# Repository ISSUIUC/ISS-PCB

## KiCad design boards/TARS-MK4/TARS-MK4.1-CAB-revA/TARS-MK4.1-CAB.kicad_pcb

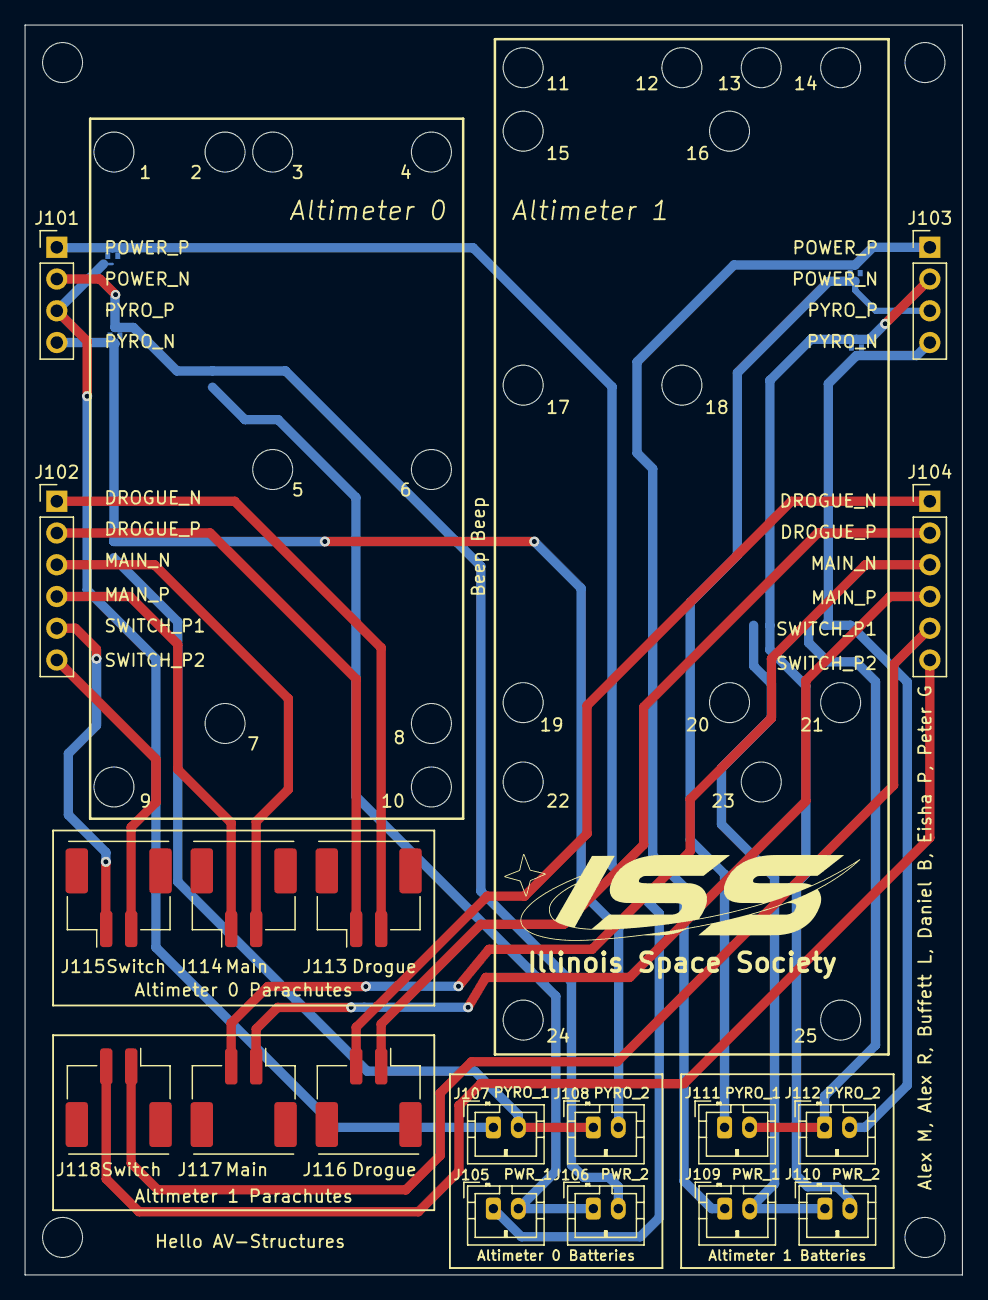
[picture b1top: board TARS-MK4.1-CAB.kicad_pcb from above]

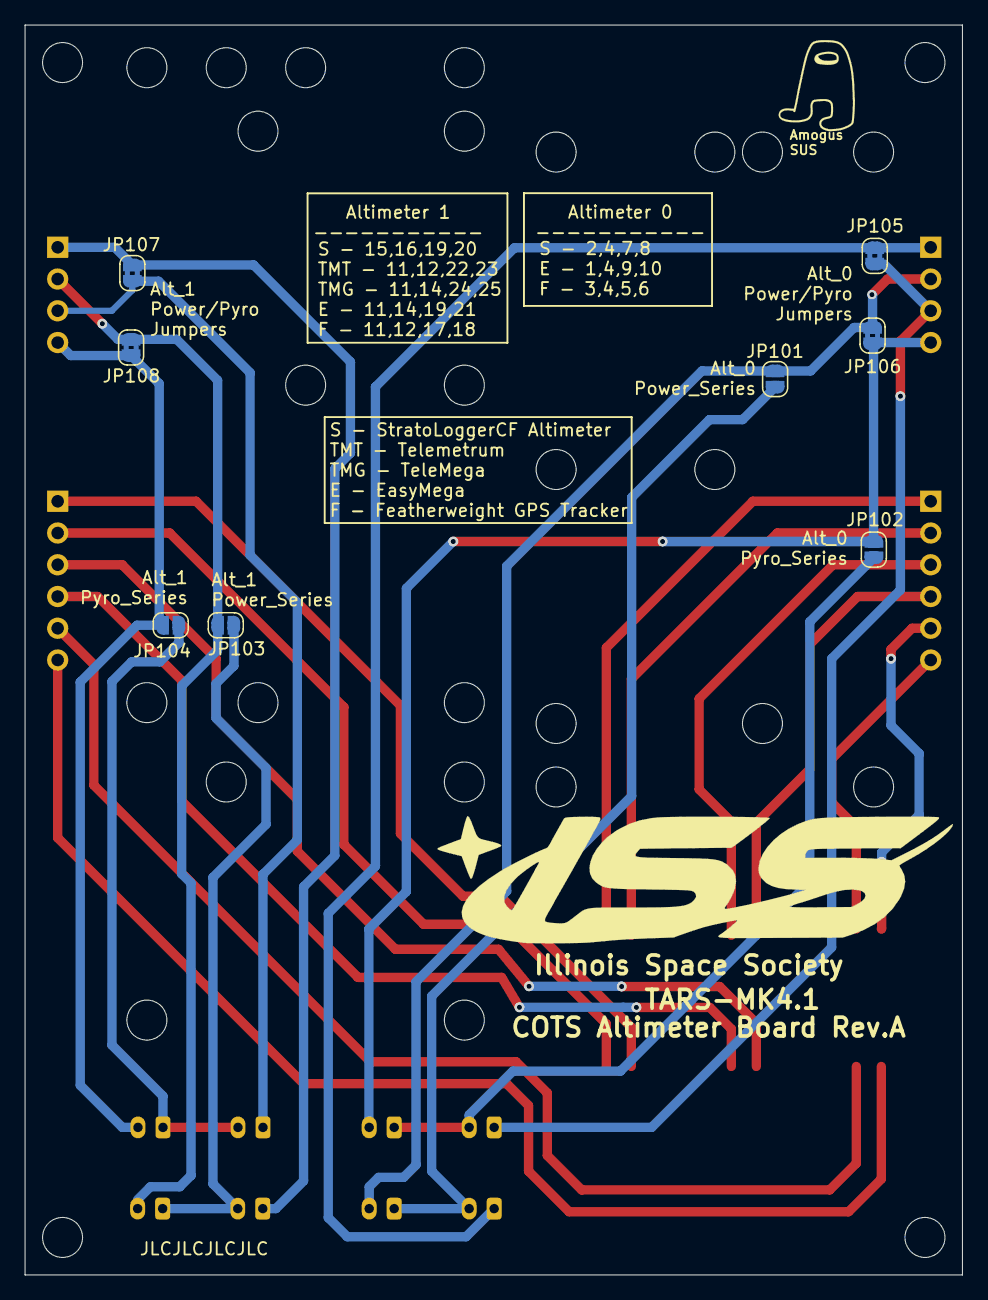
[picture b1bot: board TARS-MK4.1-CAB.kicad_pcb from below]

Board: 2 copper layers, 75.0 x 100.0 mm, 26 parts (8 on the bottom side), 24 nets.

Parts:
J101, J103: PinHeader_1x04_P2.54mm_Vertical
J102, J104: PinHeader_1x06_P2.54mm_Vertical
J105, J106, J107, J108, J109, J110, J111, J112: JST_PH_B2B-PH-K_1x02_P2.00mm_Vertical
J113, J114, J115, J116, J117, J118: Molex_CLIK-Mate_502443-0270; Molex_CLIK-Mate_502443-0270_1x02-1MP_P2.00mm_Vertical
JP101, JP102, JP103, JP104: Jumper_2_Open; SolderJumper-2_P1.3mm_Open_RoundedPad1.0x1.5mm
JP105, JP106, JP107, JP108: Jumper_2_Open; SolderJumper-2_P1.3mm_Bridged2Bar_RoundedPad1.0x1.5mm

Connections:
/ALT_0_DROGUE_A: J102.1, J113.2
/ALT_0_DROGUE_B: J102.2, J113.1
/ALT_0_MAIN_A: J102.3, J114.2
/ALT_0_MAIN_B: J102.4, J114.1
/ALT_0_POWER_N: J101.2, J106.2, JP101.1 (A), JP106.1 (A)
/ALT_0_POWER_P: J101.1, J105.1, JP105.1 (A)
/ALT_0_PYRO_N: J101.4, J108.2, JP102.1 (A), JP106.2 (B)
/ALT_0_PYRO_P: J101.3, J107.1, JP105.2 (B)
/ALT_0_SWITCH_A: J102.5, J115.1
/ALT_0_SWITCH_B: J102.6, J115.2
/ALT_1_DROGUE_A: J104.1, J116.2
/ALT_1_DROGUE_B: J104.2, J116.1
/ALT_1_MAIN_A: J104.3, J117.2
/ALT_1_MAIN_B: J104.4, J117.1
/ALT_1_POWER_N: J103.2, J110.2, JP103.1 (A), JP108.1 (A)
/ALT_1_POWER_P: J103.1, J109.1, JP107.1 (A)
/ALT_1_PYRO_N: J103.4, J112.2, JP104.1 (A), JP108.2 (B)
/ALT_1_PYRO_P: J103.3, J111.1, JP107.2 (B)
/ALT_1_SWITCH_A: J104.5, J118.1
/ALT_1_SWITCH_B: J104.6, J118.2
unnamed: J105.2, J106.1, JP101.2 (B)
unnamed: J107.2, J108.1, JP102.2 (B)
unnamed: J109.2, J110.1, JP103.2 (B)
unnamed: J111.2, J112.1, JP104.2 (B)

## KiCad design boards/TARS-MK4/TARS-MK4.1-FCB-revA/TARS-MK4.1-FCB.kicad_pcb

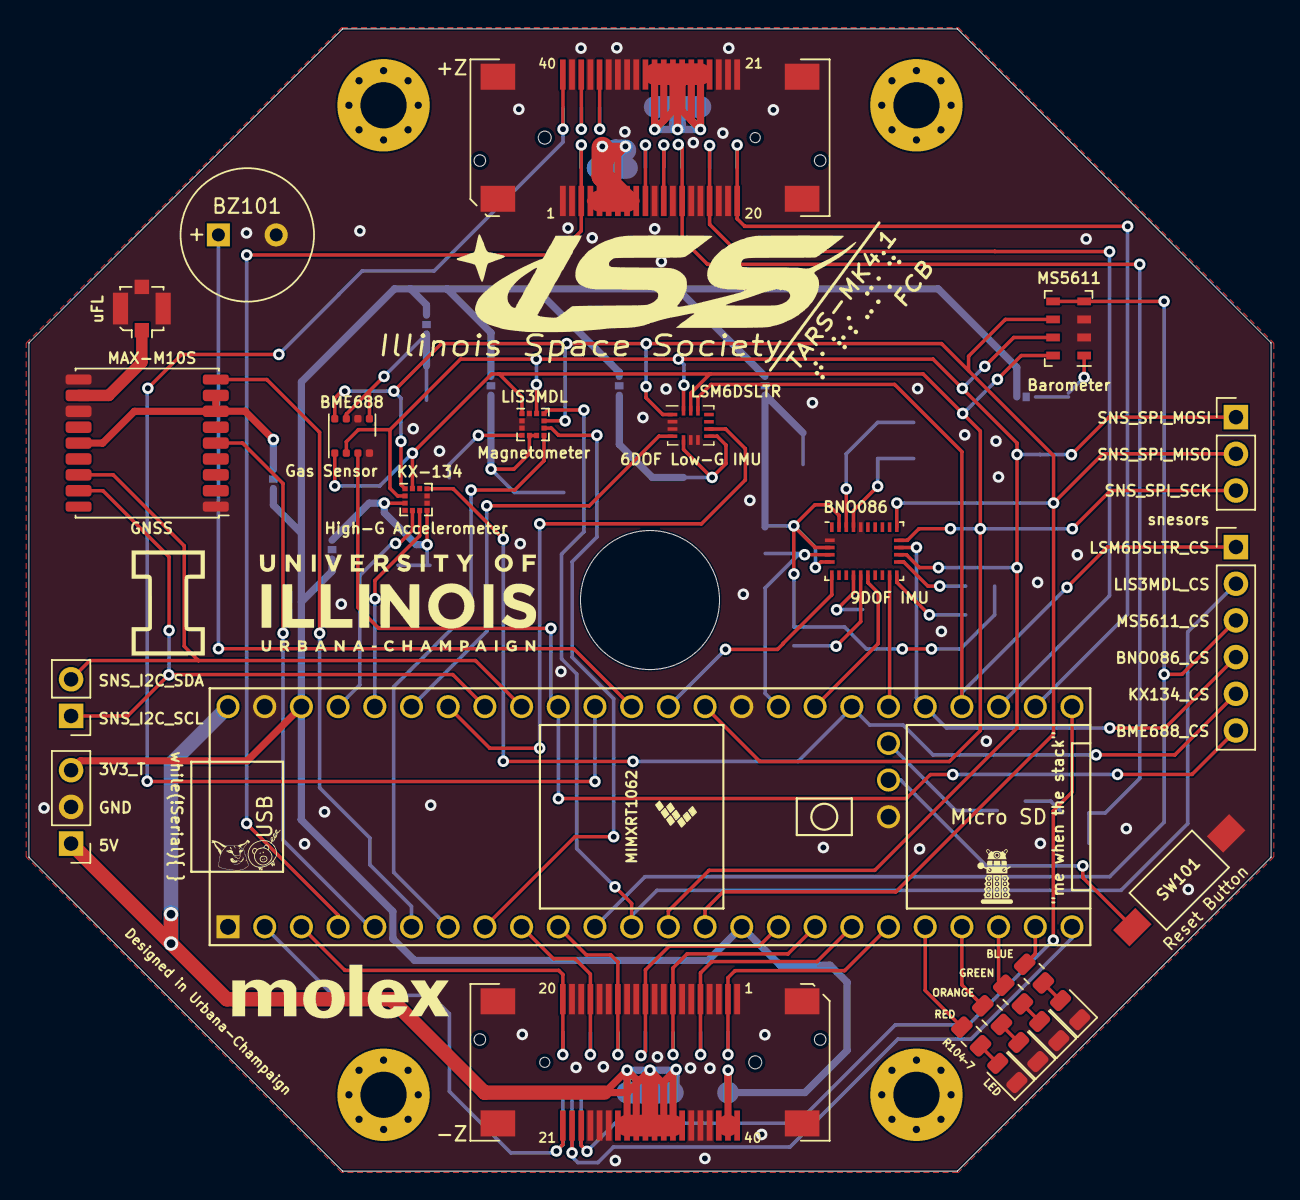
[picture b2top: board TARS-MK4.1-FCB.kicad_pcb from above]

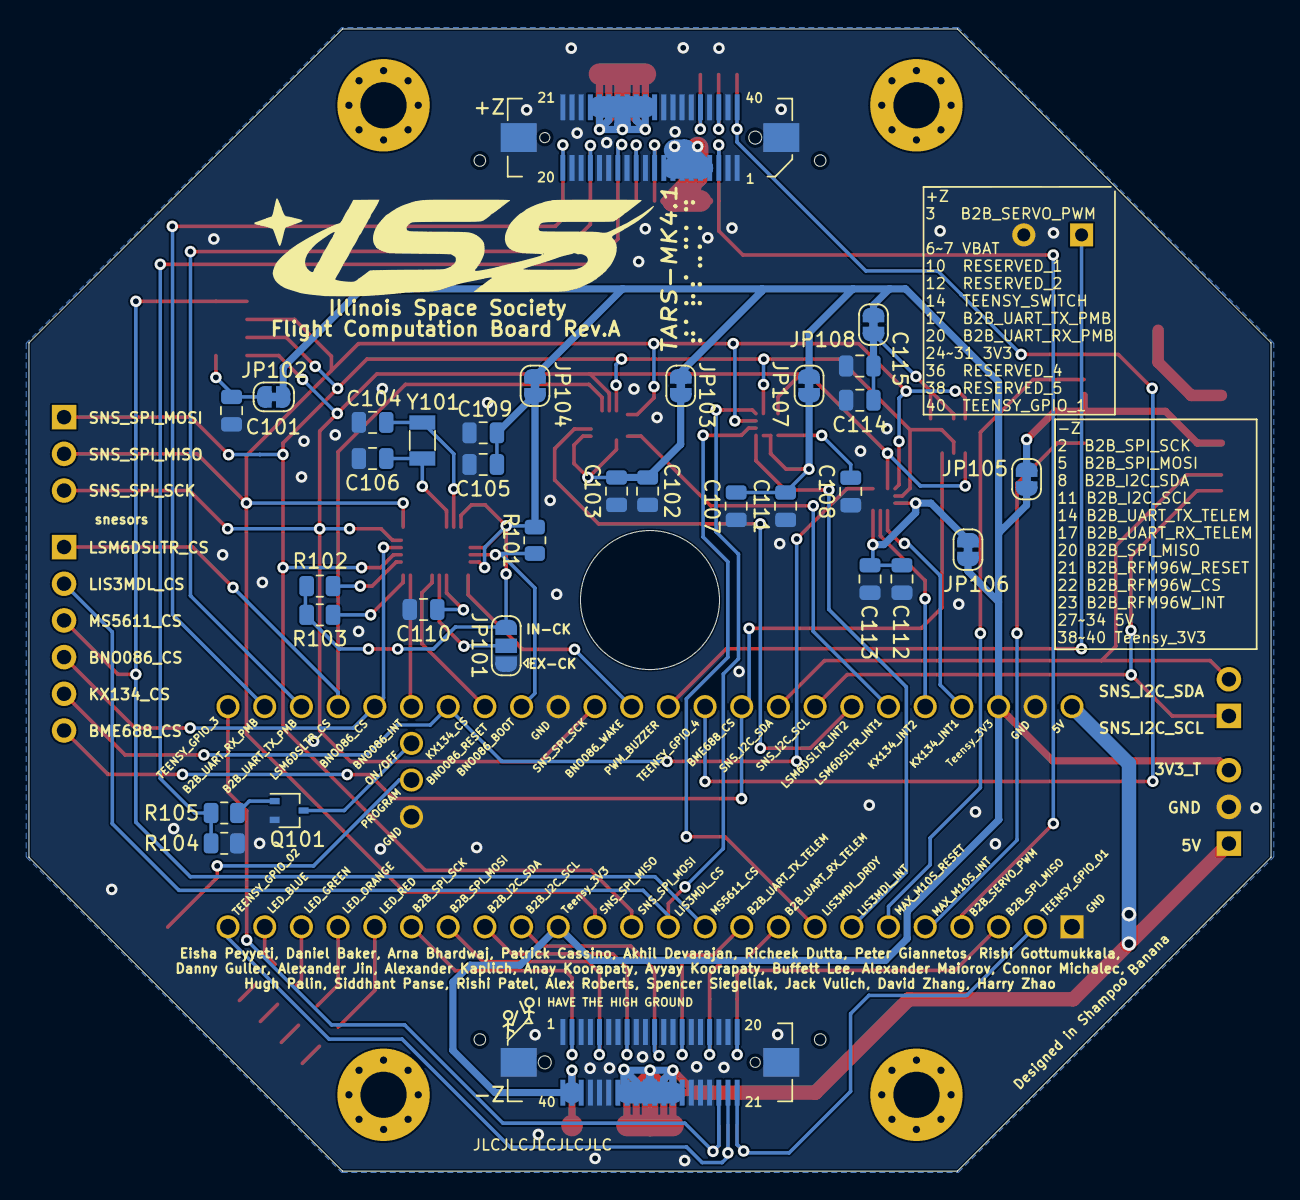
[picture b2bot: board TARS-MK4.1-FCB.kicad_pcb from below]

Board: 2 copper layers, 86.0 x 79.1 mm, 57 parts (32 on the bottom side), 74 nets.

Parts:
BZ101: Buzzer; MagneticBuzzer_PUI_AT-0927-TT-6-R
C101, C102, C103, C105, C109, C110, C112, C113, C114, C115: 0.1uF; C_0805_2012Metric
C104, C106: 22pF; C_0805_2012Metric
C107: 1uF; C_0805_2012Metric
C108, C111: 100nF; C_0805_2012Metric
D101: RED LED; LED_0805_2012Metric
D102: ORANGE LED; LED_0805_2012Metric
D103: GREEN LED; LED_0805_2012Metric
D104: BLUE LED; LED_0805_2012Metric
J101: U.FL; U.FL_Molex_MCRF_73412-0110_Vertical
J102, J103: Molex_SlimStack_2091680401_2x20_P0.635mm; Molex_SlimStack_Receptacle_2091680401_2x20_P0.635mm
J104, J105: Molex_SlimStack_Plug_550910474_2x20_P0.365mm
J106, J109: Conn_01x03; PinHeader_1x03_P2.54mm_Vertical
J107: Conn_01x02; PinHeader_1x02_P2.54mm_Vertical
J108: Conn_01x06; PinHeader_1x06_P2.54mm_Vertical
JP101: SolderJumper_3_Open; SolderJumper-3_P1.3mm_Open_RoundedPad1.0x1.5mm
JP102, JP105, JP106, JP108: Jumper_NC_Small; SolderJumper-2_P1.3mm_Bridged_RoundedPad1.0x1.5mm
JP103, JP104, JP107: Jumper_2_Bridged; SolderJumper-2_P1.3mm_Bridged_RoundedPad1.0x1.5mm
Q101: SSM3K16FU; SOT-323_SC-70
R101: 10k; R_0805_2012Metric
R102, R103: 2.2k; R_0805_2012Metric
R104: 100K; R_0805_2012Metric
R105: 100; R_0805_2012Metric
R106, R107, R108, R109: 470; R_0805_2012Metric
SW101: FSMSM Switch; SW_SPST_FSMSM
U101: MS5611-01BA03; LGA-8_3x5mm_P1.25mm
U102: LSM6DSLTR; Bosch_LGA-14_3x2.5mm_P0.5mm
U103: MAX-M10S; ublox_MAX
U104: BNO086; LGA-28_5.2x3.8mm_P0.5mm
U105: LIS3MDL; LGA-12_2x2mm_P0.5mm
U106: KX134-1211; LGA-12_2x2mm_P0.5mm
U107: Teensy4.1; Teensy41
U108: BME688; Bosch_LGA-8_3x3mm_P0.8mm_ClockwisePinNumbering
Y101: 32.768kHz; Crystal_SMD_3215-2Pin_3.2x1.5mm

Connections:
/3V3: J102.24, J102.25, J102.26, J102.27, J102.28, J102.29, J102.30, J102.31, J104.24, J104.25, J104.26, J104.27, J104.28, J104.29, J104.30, J104.31
/5V: J103.27, J103.28, J103.29, J103.30, J103.31, J103.32, J103.33, J103.34, J105.27, J105.28, J105.29, J105.30, J105.31, J105.32, J105.33, J105.34, J109.1, U107.48 (VIN)
/B2B_I2C_SCL: J103.11, J105.11, U107.16 (24_A10_TX6_SCL2)
/B2B_I2C_SDA: J103.8, J105.8, U107.17 (25_A11_RX6_SDA2)
/B2B_RFM96W_CS: J103.22, J105.22, U107.24 (32_OUT1B)
/B2B_RFM96W_INT: J103.23, J105.23, U107.25 (33_MCLK2)
/B2B_RFM96W_RESET: J103.21, J105.21, U107.2 (0_RX1_CRX2_CS1)
/B2B_SERVO_PWM: J102.3, J104.3, U107.4 (2_OUT2)
/B2B_SPI_MISO: J103.20, J105.20, U107.3 (1_TX1_CTX2_MISO1)
/B2B_SPI_MOSI: J103.5, J105.5, U107.18 (26_A12_MOSI1)
/B2B_SPI_SCK: J103.2, J105.2, U107.19 (27_A13_SCK1)
/B2B_UART_RX_PMB: J102.20, J104.20, U107.26 (34_RX8)
/B2B_UART_RX_TELEM: J103.17, J105.17, U107.9 (7_RX2_OUT1A)
/B2B_UART_TX_PMB: J102.17, J104.17, U107.27 (35_TX8)
/B2B_UART_TX_TELEM: J103.14, J105.14, U107.10 (8_TX2_IN1)
/BME688_CS: J108.6, U107.39 (17_A3_TX4_SDA1), U108.2 (CSB)
/BNO086_BOOT: R101.1, U104.4 (BOOTN), U107.33 (41_A17)
/BNO086_CS: J108.4, U104.18 (H_CSN), U107.29 (37_CS)
/BNO086_INT: U104.14 (H_INTN), U107.30 (38_CS1_IN1)
/BNO086_RESET: U104.11 (NRST), U107.32 (40_A16)
/BNO086_WAKE: U104.6 (PS0/WAKE), U107.36 (14_A0_TX3_SPDIF_OUT)
/KX134_CS: J108.5, U106.10 (nCS), U107.31 (39_MISO1_OUT1A)
/KX134_INT1: U106.5 (INT1), U107.45 (23_A9_CRX1_MCLK1)
/KX134_INT2: U106.6 (INT2), U107.44 (22_A8_CTX1)
/LED_BLUE: R109.1, U107.23 (31_CTX3)
/LED_GREEN: R108.1, U107.22 (30_CRX3)
/LED_ORANGE: R107.1, U107.21 (29_TX7)
/LED_RED: R106.1, U107.20 (28_RX7)
/LIS3MDL_CS: J108.2, U105.10 (CS), U107.12 (10_CS_MQSR)
/LIS3MDL_DRDY: U105.8 (DRDY), U107.8 (6_OUT1D)
/LIS3MDL_INT: U105.7 (INT), U107.7 (5_IN2)
/LSM6DSLTR_CS: J108.1, U102.12 (CS), U107.28 (36_CS)
/LSM6DSLTR_INT1: U102.4 (INT1), U107.43 (21_A7_RX5_BCLK1)
/LSM6DSLTR_INT2: U102.9 (INT2), U107.42 (20_A6_TX5_LRCLK1)
/MAX-M10S_INT: U103.5 (EXTINT), U107.5 (3_LRCLK2)
/MAX-M10S_RESET: U103.9 (RESET_N), U107.6 (4_BCLK2)
/MS5611_CS: J108.3, U101.4 (CSB), U101.5 (CSB), U107.11 (9_OUT1C)
/PROGRAM: SW101.1, U107.53 (PROGRAM)
/PWM_BUZZER: BZ101.1 (-), U107.37 (15_A1_RX3_SPDIF_IN)
/RESERVED_1: J102.10, J104.10
/RESERVED_2: J102.12, J104.12
/RESERVED_3: J102.36, J104.36
/RESERVED_4: J102.38, J104.38
/SNS_I2C_SCL: J107.1, U103.17 (SCL), U107.41 (19_A5_SCL)
/SNS_I2C_SDA: J107.2, U103.16 (SDA), U107.40 (18_A4_SDA)
/SNS_SPI_MISO: J106.2, U101.6 (SDO), U102.1 (SDO/SA0), U104.20 (H_SDA/H_MISO/TX), U105.9 (SDO/SA1), U106.1 (SDO/ADDR), U107.14 (12_MISO_MQSL), U108.5 (SDO)
/SNS_SPI_MOSI: J106.1, U101.7 (SDI/SDA), U102.14 (SDA), U104.17 (H_SA0_MOSI), U105.11 (SDA/SDI/SDO), U106.2 (SDI/SDA), U107.13 (11_MOSI_CTX1), U108.3 (SDI)
/SNS_SPI_SCK: J106.3, U101.8 (SCLK), U102.13 (SCL), U104.19 (H_SCL/SCK/RX), U105.1 (SCL/SPC), U106.12 (SCLK/SCL), U107.35 (13_SCK_LED), U108.4 (SCK)
/TEENSY_GPIO_1: J102.40, J104.40, U107.38 (16_A2_RX4_SCL1)
/TEENSY_ON/OFF: Q101.3 (D), U107.54 (On/Off)
/TEENSY_SWITCH: J102.14, J104.14, R104.1, R105.2
/Teensy_3V3: J103.38, J103.39, J103.40, J105.38, J105.39, J105.40, J109.3, JP102.1 (A), JP103.1 (A), JP104.2 (B), JP105.1 (A), JP106.1 (A), JP107.1 (A), JP108.1 (A), U107.15 (3V3), U107.46 (3V3)
/VBAT: J102.4, J102.5, J102.6, J102.7, J102.8, J102.9, J104.4, J104.5, J104.6, J104.7, J104.8, J104.9
GND: BZ101.2 (+), C101.1, C102.1, C103.1, C104.2, C105.2, C106.2, C107.1, C108.1, C109.2, C110.2, C111.1, C112.2, C113.1, C114.2, C115.1, D101.1 (K), D102.1 (K), D103.1 (K), D104.1 (K), J101.2 (Ext), J102.1, J102.2, J102.11, J102.13, J102.15, J102.16, J102.18, J102.19, J102.21, J102.22, J102.23, J102.32, J102.33, J102.34, J102.35, J102.37, J102.39, J102.MP (MountPin), J103.1, J103.3, J103.4, J103.6, J103.7, J103.9, J103.10, J103.12, J103.13, J103.15, J103.16, J103.18, J103.19, J103.24, J103.25, J103.26, J103.35, J103.36, J103.37, J103.MP (MountPin), J104.1, J104.2, J104.11, J104.13, J104.15, J104.16, J104.18, J104.19, J104.21, J104.22, J104.23, J104.32, J104.33, J104.34, J104.35, J104.37, J104.39, J104.MP (MountPin), J105.1, J105.3, J105.4, J105.6, J105.7, J105.9, J105.10, J105.12, J105.13, J105.15, J105.16, J105.18, J105.19, J105.24, J105.25, J105.26, J105.35, J105.36, J105.37, J105.MP (MountPin), J109.2, JP101.1 (A), Q101.2 (S), R104.2, SW101.2, U101.2 (PS), U101.3 (GND), U102.2 (SDX), U102.3 (SCX), U102.6 (GND), U102.7 (GND), U103.1 (GND), U103.10 (GND), U103.12 (GND), U104.2 (GND), U104.25 (GNDIO), U105.2 (GND), U105.3 (GND), U105.12 (GND), U106.4 (TRIG), U106.8 (GND), U106.9 (GND), U107.1 (GND), U107.34 (GND), U107.47 (GND), U107.52 (GND), U108.1 (GND), U108.7 (GND)
unnamed: C101.2, JP102.2 (B), U101.1 (VDD)
unnamed: C102.2, C103.2, JP103.2 (B), U102.5 (VDDIO), U102.8 (VDD)
unnamed: C104.1, U104.27 (XIN32), Y101.1
unnamed: C105.1, C109.1, JP101.3 (B), JP104.1 (A), R101.2, R102.2, R103.2, U104.3 (VDD), U104.5 (PS1), U104.28 (VDDIO)
unnamed: C106.1, U104.26 (XOUT32/CLKSEL1), Y101.2
unnamed: C107.2, C111.2, JP107.2 (B), U105.5 (VDD), U105.6 (VDD_IO)
unnamed: C108.2, U105.4 (C1)
unnamed: C110.1, U104.9 (CAP)
unnamed: C112.1, C113.2, JP106.2 (B), U106.3 (VDDIO), U106.7 (VDD)
unnamed: C114.1, C115.2, JP108.2 (B), U108.6 (VDDIO), U108.8 (VDD)
unnamed: D101.2 (A), R106.2
unnamed: D102.2 (A), R107.2
unnamed: D103.2 (A), R108.2
unnamed: D104.2 (A), R109.2
unnamed: J101.1 (In), U103.11 (RF_IN)
unnamed: JP101.2 (C), U104.10 (CLKSEL0)
unnamed: JP105.2 (B), U103.7 (V_IO), U103.8 (VCC), U103.14 (VCC_RF)
unnamed: Q101.1 (G), R105.1
unnamed: R102.1, U104.16 (ENV_SDA)
unnamed: R103.1, U104.15 (ENV_SCL)

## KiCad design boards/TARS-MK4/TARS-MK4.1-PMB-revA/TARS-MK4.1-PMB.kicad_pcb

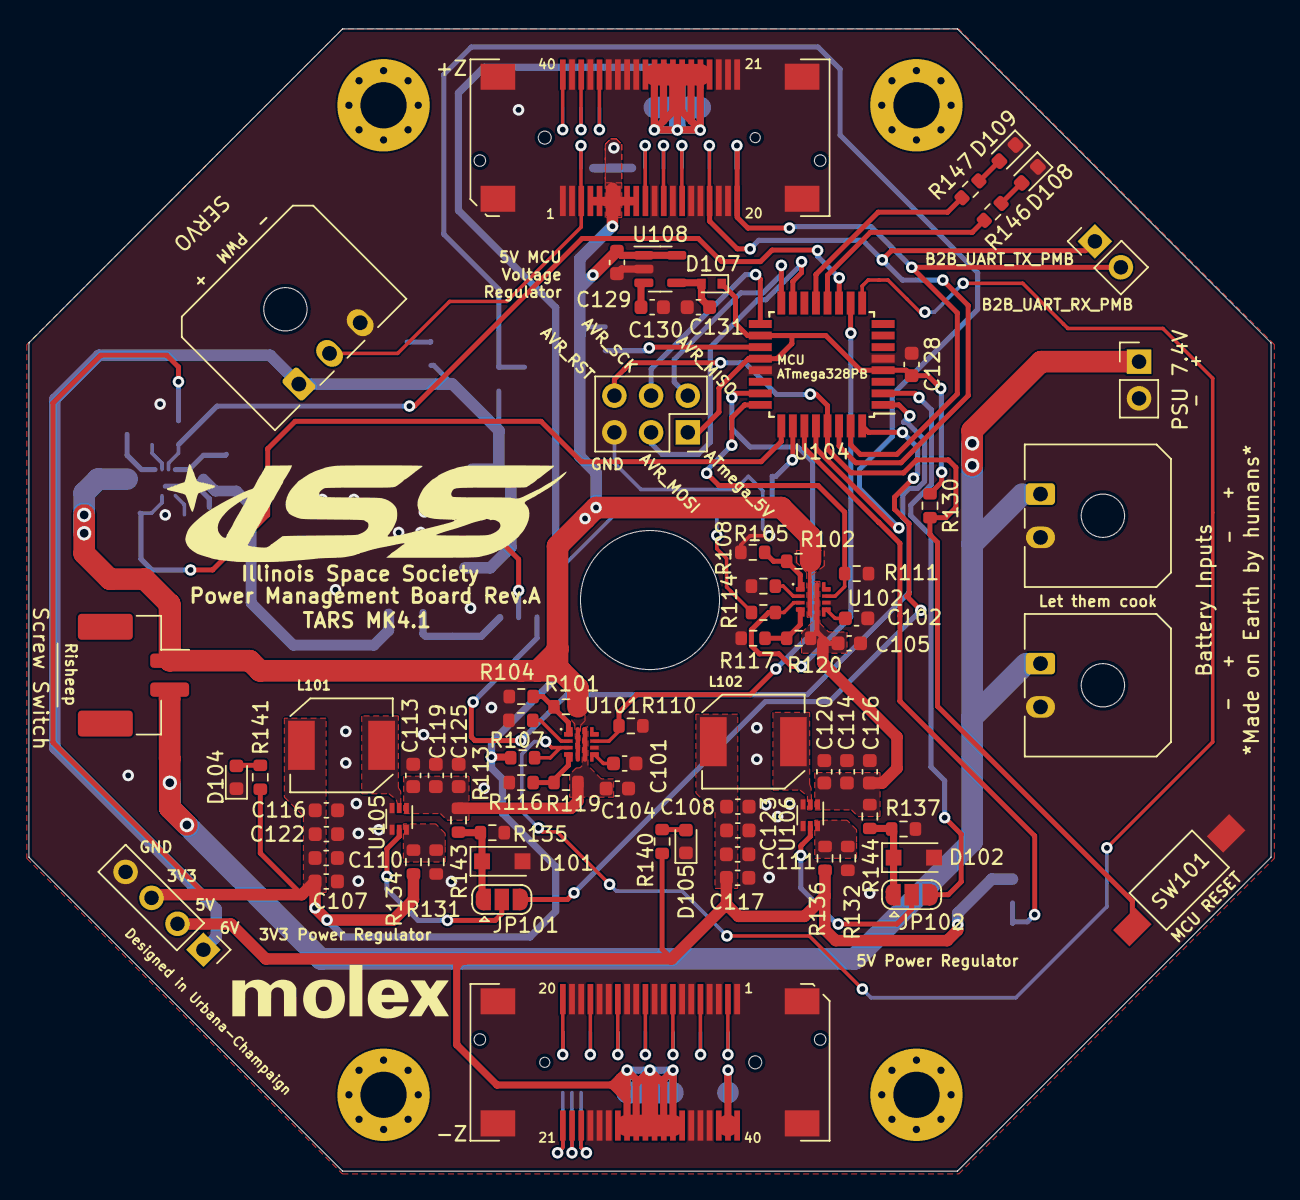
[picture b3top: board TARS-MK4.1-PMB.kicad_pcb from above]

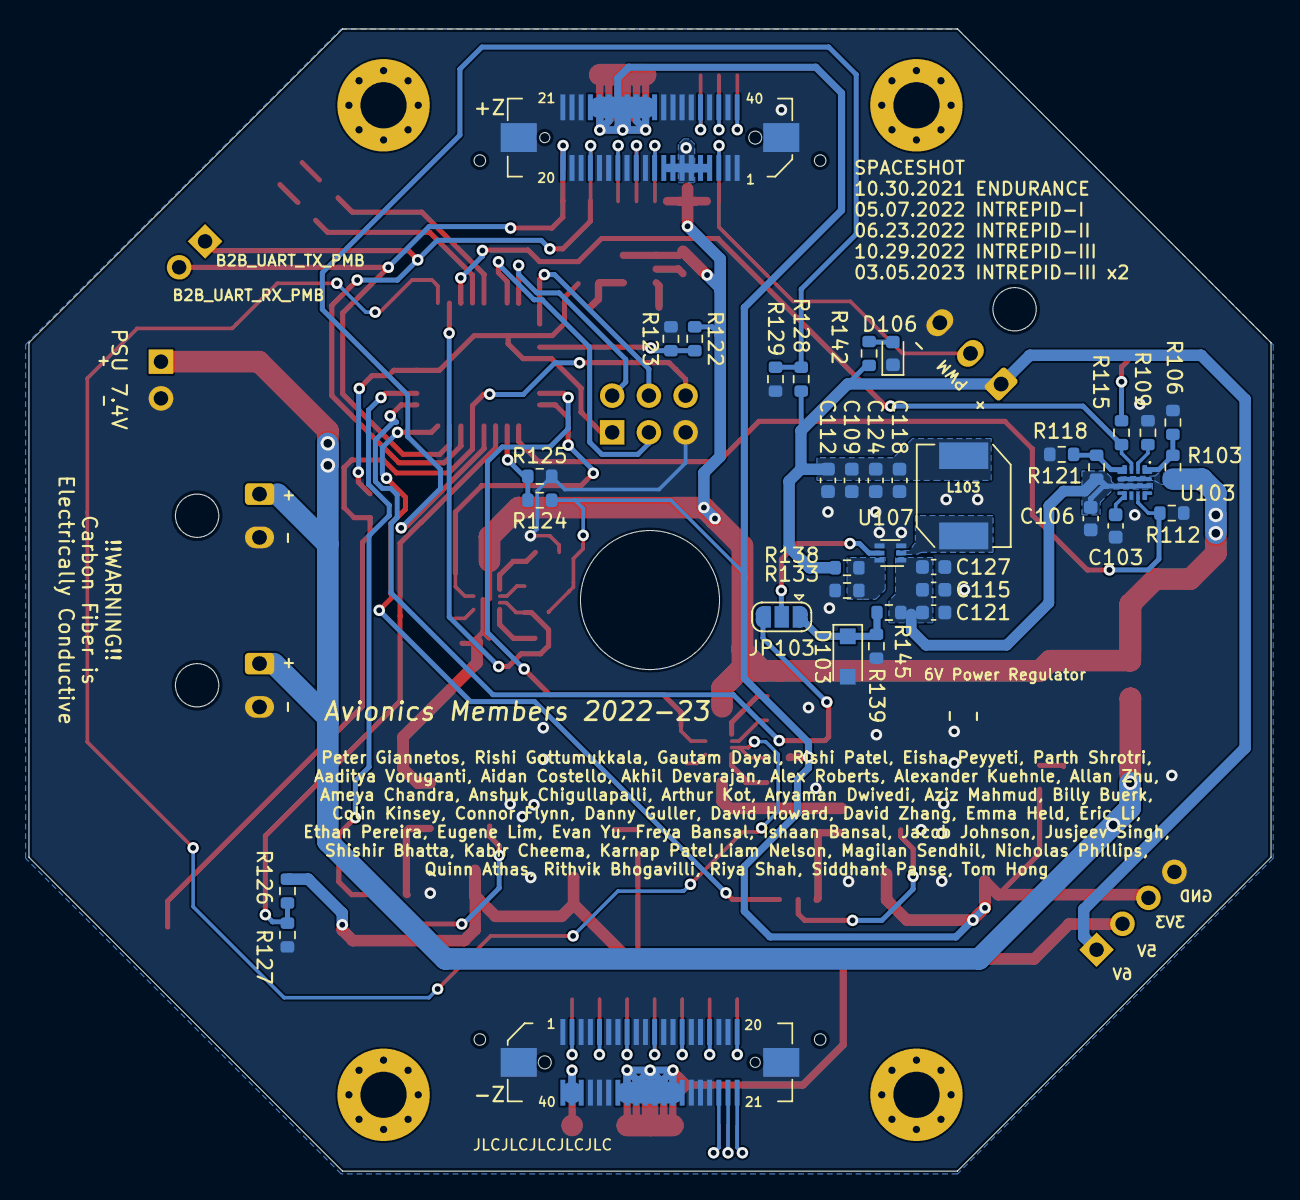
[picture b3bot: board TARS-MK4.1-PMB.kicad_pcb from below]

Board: 2 copper layers, 86.0 x 79.1 mm, 114 parts (37 on the bottom side), 80 nets.

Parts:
C101, C102, C103: 5.1nF; C_0603_1608Metric
C104, C105, C106: 470uF; C_0603_1608Metric
C107, C108, C109, C110, C111, C112, C116, C117, C118, C122, C123, C124: 22uF; C_0603_1608Metric
C113, C114, C115, C119, C120, C121: 10uF; C_0603_1608Metric
C125, C126, C127, C130: 0.1uF; C_0603_1608Metric
C128: 100nF; C_0603_1608Metric
C129: 1uF; C_0603_1608Metric
C131: 2.2uF; C_0603_1608Metric
D101, D102, D103: BZT52H-A5V1-QX; D_SOD-123F
D104, D105, D106: RED; LED_0603_1608Metric
D107: NSVRB751S40T1G; D_SOD-523
D108: GREEN; LED_0603_1608Metric
D109: ORANGE; LED_0603_1608Metric
J101: Molex Micro-Fit 436500300; Molex_Micro-Fit_3.0_43650-0300_1x03_P3.00mm_Horizontal
J102: Molex Micro-Lock 5055780271; Molex_CLIK-Mate_502494-0270_1x02-1MP_P2.00mm_Horizontal
J103, J104: Molex Micro-Fit 436500200; Molex_Micro-Fit_3.0_43650-0200_1x02_P3.00mm_Horizontal
J105, J109: Conn_01x02; PinHeader_1x02_P2.54mm_Vertical
J106, J107: Molex_SlimStack_2091680401_2x20_P0.635mm; Molex_SlimStack_Receptacle_2091680401_2x20_P0.635mm
J108: Conn_01x04; PinHeader_1x04_P2.54mm_Vertical
J110, J111: Molex_SlimStack_Plug_550910474_2x20_P0.365mm
J112: AVR_ISP; PinSocket_2x03_P2.54mm_Vertical
JP101, JP102, JP103: SolderJumper_3_Open; SolderJumper-3_P1.3mm_Open_RoundedPad1.0x1.5mm
L101, L102: 2.2uH; L_TDK_SPM6530
L103: 3.3uH; L_TDK_SPM6530
R101, R102, R103, R119, R120, R121: 470k; R_0603_1608Metric
R104, R105, R116, R117, R118: 120k; R_0603_1608Metric
R106: 105k; R_0603_1608Metric
R107, R108, R109: 390k; R_0603_1608Metric
R110, R111, R112: 866; R_0603_1608Metric
R113, R114, R115: 47k; R_0603_1608Metric
R122: 200k; R_0603_1608Metric
R123, R124, R125, R126, R127, R128, R129: 100k; R_0603_1608Metric
R130: 10k; R_0603_1608Metric
R131, R132, R133, R135, R137, R139: 30k; R_0603_1608Metric
R134: 135k; R_0603_1608Metric
R136: 220k; R_0603_1608Metric
R138: 270k; R_0603_1608Metric
R140: 715; R_0603_1608Metric
R141: 470; R_0603_1608Metric
R142: 845; R_0603_1608Metric
R143, R144, R145: 20k; R_0603_1608Metric
R146, R147: 150; R_0603_1608Metric
SW101: SW_Push; SW_SPST_FSMSM
U101, U102, U103: TPS25947; VQFN-HR-RPW0010A
U104: ATmega328PB-A; TQFP-32_7x7mm_P0.8mm
U105, U106, U107: TI_TPS566242DRLR; SOT-563
U108: LK112M50TR; SOT-23-5

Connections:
/3V3: C107.1, C110.1, C116.1, C122.1, J106.24, J106.25, J106.26, J106.27, J106.28, J106.29, J106.30, J106.31, J108.3, J110.24, J110.25, J110.26, J110.27, J110.28, J110.29, J110.30, J110.31, L101.1, R113.2, R114.2, R115.2, R124.1, R134.2, R141.1
/3V3_EN_JMP: JP101.2 (C), U105.5 (EN)
/3V3_EN_MCU: JP101.3 (B), U104.32 (PD2)
/3V3_EN_VBAT: D101.1 (K), JP101.1 (A), R135.1, R143.1
/3V3_FB: R131.1, R134.1, U105.6 (FB)
/3V3_LED: D104.2 (A), R141.2
/3V3_SENSE: R124.2, R125.1, U104.26 (PC3)
/3V3_SW: L101.2, U105.2 (SW)
/5V: C108.1, C111.1, C117.1, C123.1, J107.27, J107.28, J107.29, J107.30, J107.31, J107.32, J107.33, J107.34, J108.2, J111.27, J111.28, J111.29, J111.30, J111.31, J111.32, J111.33, J111.34, L102.1, R126.1, R136.2, R140.1
/5V_EN_JMP: JP102.2 (C), U106.5 (EN)
/5V_EN_MCU: JP102.3 (B), U104.2 (PD4)
/5V_EN_VBAT: D102.1 (K), JP102.1 (A), R137.1, R144.1
/5V_FB: R132.1, R136.1, U106.6 (FB)
/5V_LED: D105.2 (A), R140.2
/5V_MCU_BP: C130.1, U108.3 (Bypass)
/5V_MCU_DIODE: C131.1, D107.2 (A), U108.4 (OUT)
/5V_SENSE: R126.2, R127.1, U104.27 (PC4)
/5V_SW: L102.2, U106.2 (SW)
/6V: C109.1, C112.1, C118.1, C124.1, J101.1, J108.1, L103.1, R128.1, R138.2, R142.1
/6V_EN_JMP: JP103.2 (C), U107.5 (EN)
/6V_EN_MCU: JP103.3 (B), U104.1 (PD3)
/6V_EN_VBAT: D103.1 (K), JP103.1 (A), R139.1, R145.1
/6V_FB: R133.1, R138.1, U107.6 (FB)
/6V_LED: D106.2 (A), R142.2
/6V_SENSE: R128.2, R129.1, U104.28 (PC5)
/6V_SW: L103.2, U107.2 (SW)
/ATmega_5V: C128.1, D107.1 (K), J112.1, R130.1, U104.4 (VCC), U104.18 (AVCC), U104.20 (AREF)
/AVR_MISO: J112.2, U104.16 (PB4)
/AVR_MOSI: J112.3, U104.15 (PB3)
/AVR_RST: J112.6, R130.2, SW101.1, U104.29 (~RESET/PC6)
/AVR_SCK: J112.4, U104.17 (PB5)
/B2B_I2C_SCL: J107.11, J111.11
/B2B_I2C_SDA: J107.8, J111.8
/B2B_RFM96W_CS: J107.22, J111.22
/B2B_RFM96W_INT: J107.23, J111.23
/B2B_RFM96W_RESET: J107.21, J111.21
/B2B_SERVO_PWM: J101.2, J106.3, J110.3
/B2B_SPI_MISO: J107.20, J111.20
/B2B_SPI_MOSI: J107.5, J111.5
/B2B_SPI_SCK: J107.2, J111.2
/B2B_UART_RX_PMB: J106.20, J109.2, J110.20, U104.31 (PD1)
/B2B_UART_RX_TELEM: J107.17, J111.17
/B2B_UART_TX_PMB: J106.17, J109.1, J110.17, U104.30 (PD0)
/B2B_UART_TX_TELEM: J107.14, J111.14
/DVDT_3V3: C101.1, U101.7 (DVDT)
/DVDT_5V: C102.1, U102.7 (DVDT)
/DVDT_6V: C103.1, U103.7 (DVDT)
/ILM _3V3: R110.2, U101.9 (ILM), U104.23 (PC0)
/ILM_5V: R111.2, U102.9 (ILM), U104.24 (PC1)
/ILM_6V: R112.2, U103.9 (ILM), U104.25 (PC2)
/LED_GREEN: R146.1, U104.12 (PB0)
/LED_ORANGE: R147.1, U104.13 (PB1)
/OVLO_3V3: R107.1, U101.2 (OVLO/OVCSEL)
/OVLO_5V: R108.1, U102.2 (OVLO/OVCSEL)
/OVLO_6V: R109.1, U103.2 (OVLO/OVCSEL)
/PGTH_3V3: R116.1, R119.1, U101.4 (PGTH/NFLT)
/PGTH_5V: R117.1, R120.1, U102.4 (PGTH/NFLT)
/PGTH_6V: R118.1, R121.1, U103.4 (PGTH/NFLT)
/PG_3V3: R113.1, U101.3 (PG/AUXOFF), U104.9 (PD5)
/PG_5V: R114.1, U102.3 (PG/AUXOFF), U104.10 (PD6)
/PG_6V: R115.1, U103.3 (PG/AUXOFF), U104.11 (PD7)
/PSU_RAW: J102.2, J103.1, J104.1, J105.1
/RESERVED_1: J106.10, J110.10
/RESERVED_2: J106.12, J110.12
/RESERVED_3: J106.36, J110.36
/RESERVED_4: J106.38, J110.38
/STATUS_G: D108.2 (A), R146.2
/STATUS_R: D109.2 (A), R147.2
/TEENSY_GPIO_1: J106.40, J110.40
/TEENSY_SWITCH: J106.14, J110.14
/Teensy_3V3: J107.38, J107.39, J107.40, J111.38, J111.39, J111.40
/UVLO_3V3: R101.2, R104.1, U101.1 (EN/UVLO)
/UVLO_5V: R102.2, R105.1, U102.1 (EN/UVLO)
/UVLO_6V: R103.2, R106.1, U103.1 (EN/UVLO)
/VBAT: C129.1, J102.1, J106.4, J106.5, J106.6, J106.7, J106.8, J106.9, J110.4, J110.5, J110.6, J110.7, J110.8, J110.9, R101.1, R102.1, R103.1, R122.1, U101.5 (IN), U102.5 (IN), U103.5 (IN), U108.1 (SHDN), U108.5 (IN)
/VBAT_3V3: C104.1, C113.1, C119.1, C125.1, R119.2, R143.2, U101.6 (OUT), U105.1 (VIN)
/VBAT_5V: C105.1, C114.1, C120.1, C126.1, R120.2, R144.2, U102.6 (OUT), U106.1 (VIN)
/VBAT_6V: C106.1, C115.1, C121.1, C127.1, R121.2, R145.2, U103.6 (OUT), U107.1 (VIN)
/VBAT_SENSE: R122.2, R123.1, U104.19 (PE2)
GND: C101.2, C102.2, C103.2, C104.2, C105.2, C106.2, C107.2, C108.2, C109.2, C110.2, C111.2, C112.2, C113.2, C114.2, C115.2, C116.2, C117.2, C118.2, C119.2, C120.2, C121.2, C122.2, C123.2, C124.2, C125.2, C126.2, C127.2, C128.2, C129.2, C130.2, C131.2, D101.2 (A), D102.2 (A), D103.2 (A), D104.1 (K), D105.1 (K), D106.1 (K), D108.1 (K), D109.1 (K), J101.3, J103.2, J104.2, J105.2, J106.1, J106.2, J106.11, J106.13, J106.15, J106.16, J106.18, J106.19, J106.21, J106.22, J106.23, J106.32, J106.33, J106.34, J106.35, J106.37, J106.39, J106.MP (MountPin), J107.1, J107.3, J107.4, J107.6, J107.7, J107.9, J107.10, J107.12, J107.13, J107.15, J107.16, J107.18, J107.19, J107.24, J107.25, J107.26, J107.35, J107.36, J107.37, J107.MP (MountPin), J108.4, J110.1, J110.2, J110.11, J110.13, J110.15, J110.16, J110.18, J110.19, J110.21, J110.22, J110.23, J110.32, J110.33, J110.34, J110.35, J110.37, J110.39, J110.MP (MountPin), J111.1, J111.3, J111.4, J111.6, J111.7, J111.9, J111.10, J111.12, J111.13, J111.15, J111.16, J111.18, J111.19, J111.24, J111.25, J111.26, J111.35, J111.36, J111.37, J111.MP (MountPin), J112.5, R104.2, R105.2, R106.2, R107.2, R108.2, R109.2, R110.1, R111.1, R112.1, R116.2, R117.2, R118.2, R123.2, R125.2, R127.2, R129.2, R131.2, R132.2, R133.2, R135.2, R137.2, R139.2, SW101.2, U101.8 (GND), U102.8 (GND), U103.8 (GND), U104.5 (GND), U104.21 (GND), U105.3 (GND), U105.4 (AGND), U106.3 (GND), U106.4 (AGND), U107.3 (GND), U107.4 (AGND), U108.2 (GND)
